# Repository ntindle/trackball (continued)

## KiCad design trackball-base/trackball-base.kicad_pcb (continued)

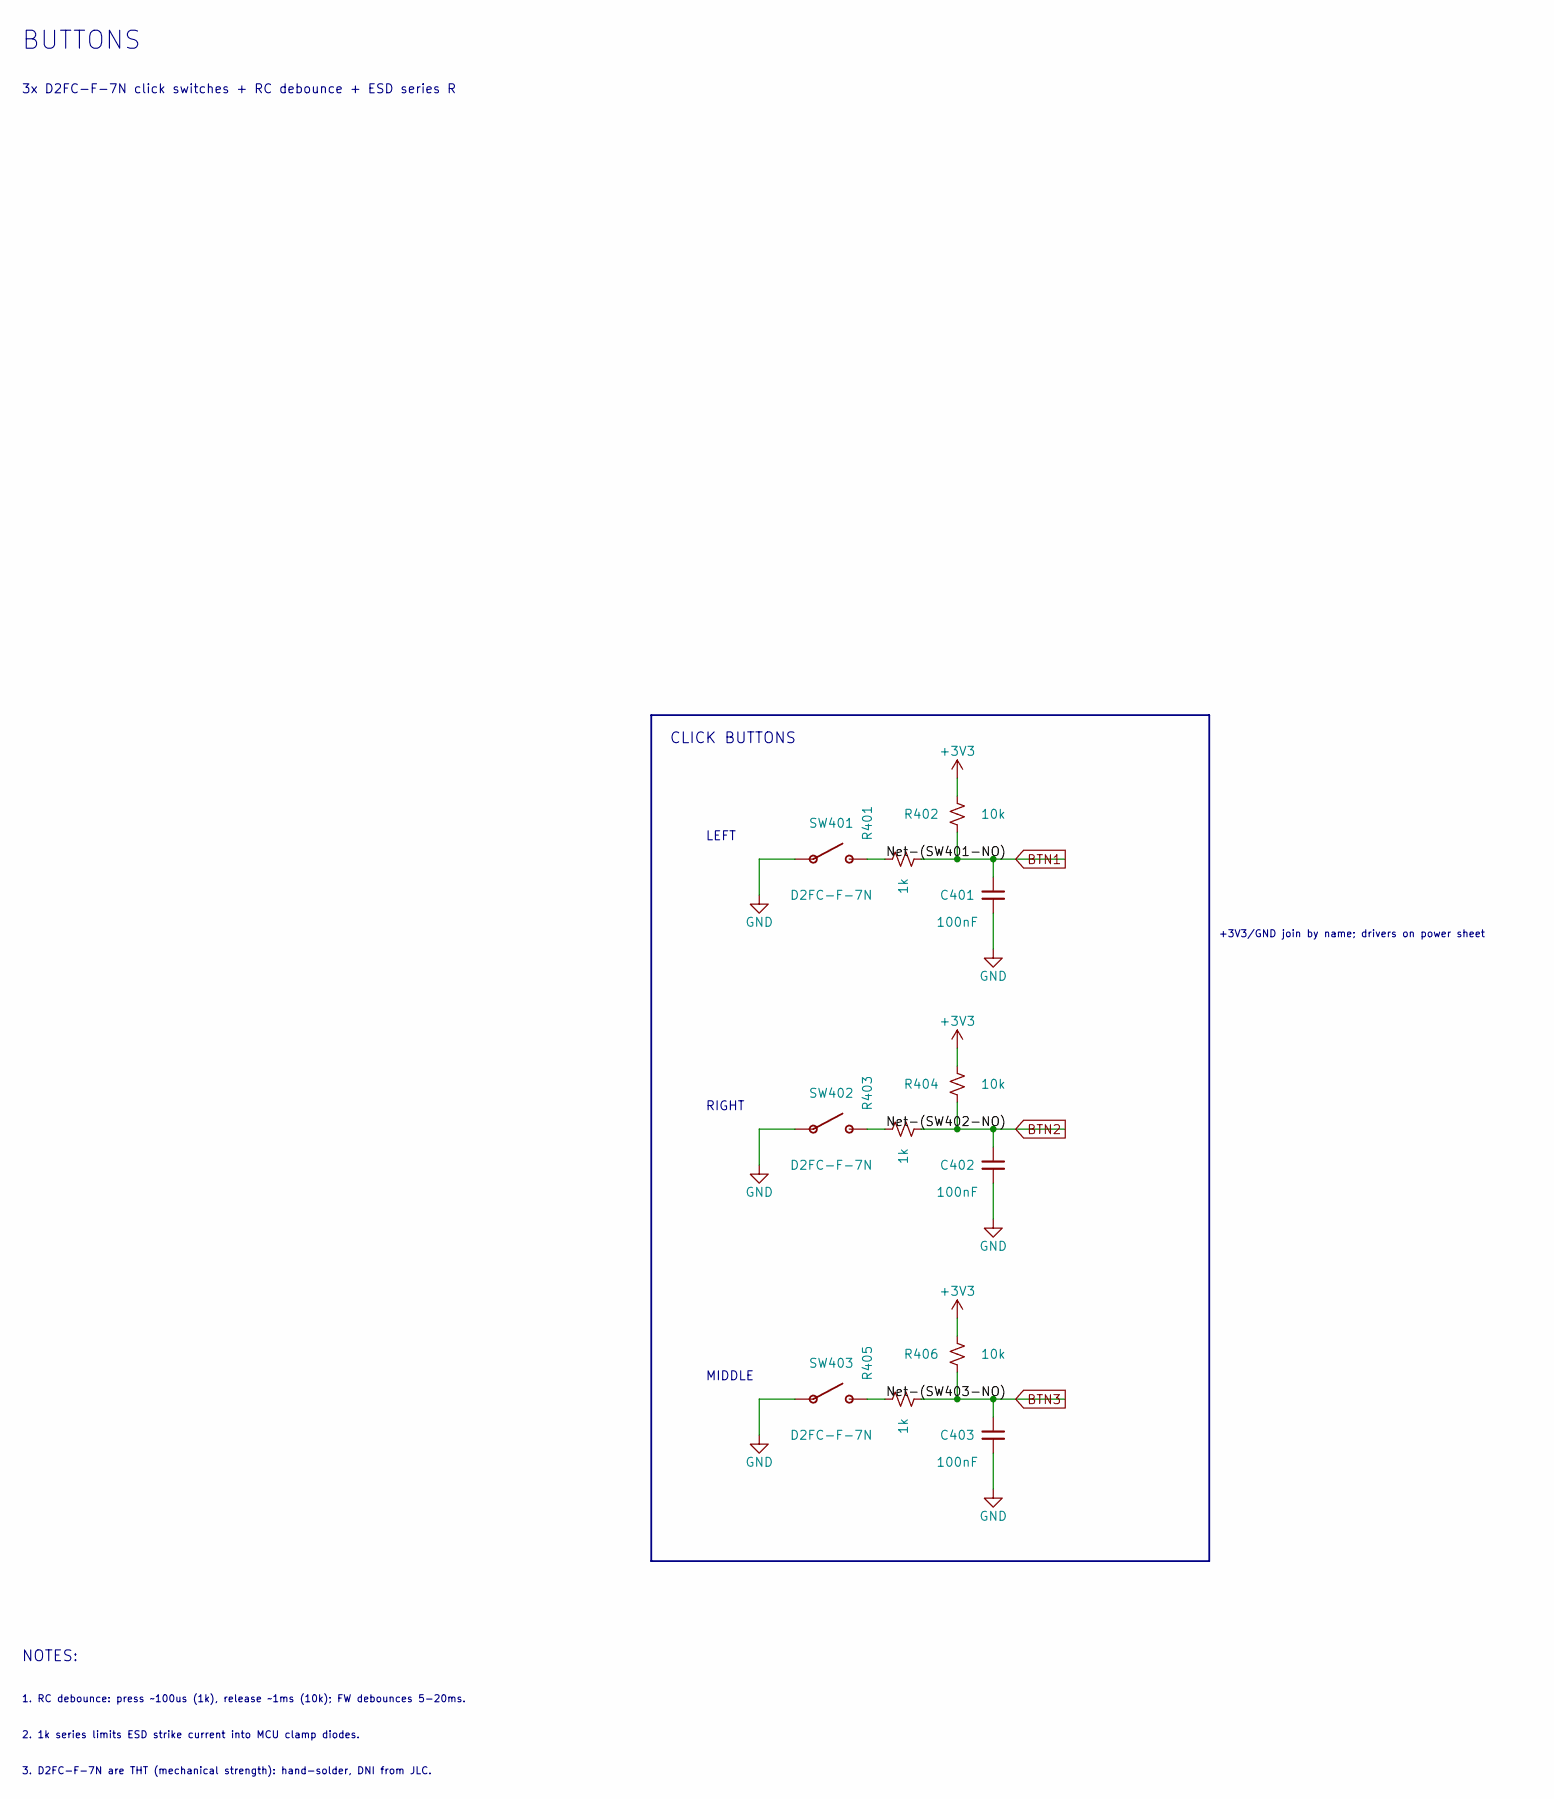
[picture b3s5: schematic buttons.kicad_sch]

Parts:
C401, C402, C403: 100nF; C_0603_1608Metric
R401, R403, R405: 1k; R_0603_1608Metric
R402, R404, R406: 10k; R_0603_1608Metric
SW401, SW402, SW403: D2FC-F-7N

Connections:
+3V3: R402.1, R404.1, R406.1; also elsewhere on the board
/buttons/Net-(SW401-NO): R401.1, SW401.2 (NO)
/buttons/Net-(SW402-NO): R403.1, SW402.2 (NO)
/buttons/Net-(SW403-NO): R405.1, SW403.2 (NO)
BTN1: C401.1, R401.2, R402.2; also elsewhere on the board
BTN2: C402.1, R403.2, R404.2; also elsewhere on the board
BTN3: C403.1, R405.2, R406.2; also elsewhere on the board

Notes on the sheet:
BUTTONS
3x D2FC-F-7N click switches + RC debounce + ESD series R
CLICK BUTTONS
LEFT
RIGHT
MIDDLE
+3V3/GND join by name; drivers on power sheet
NOTES:
1. RC debounce: press ~100us (1k), release ~1ms (10k); FW debounces 5-20ms.
2. 1k series limits ESD strike current into MCU clamp diodes.
3. D2FC-F-7N are THT (mechanical strength): hand-solder, DNI from JLC.

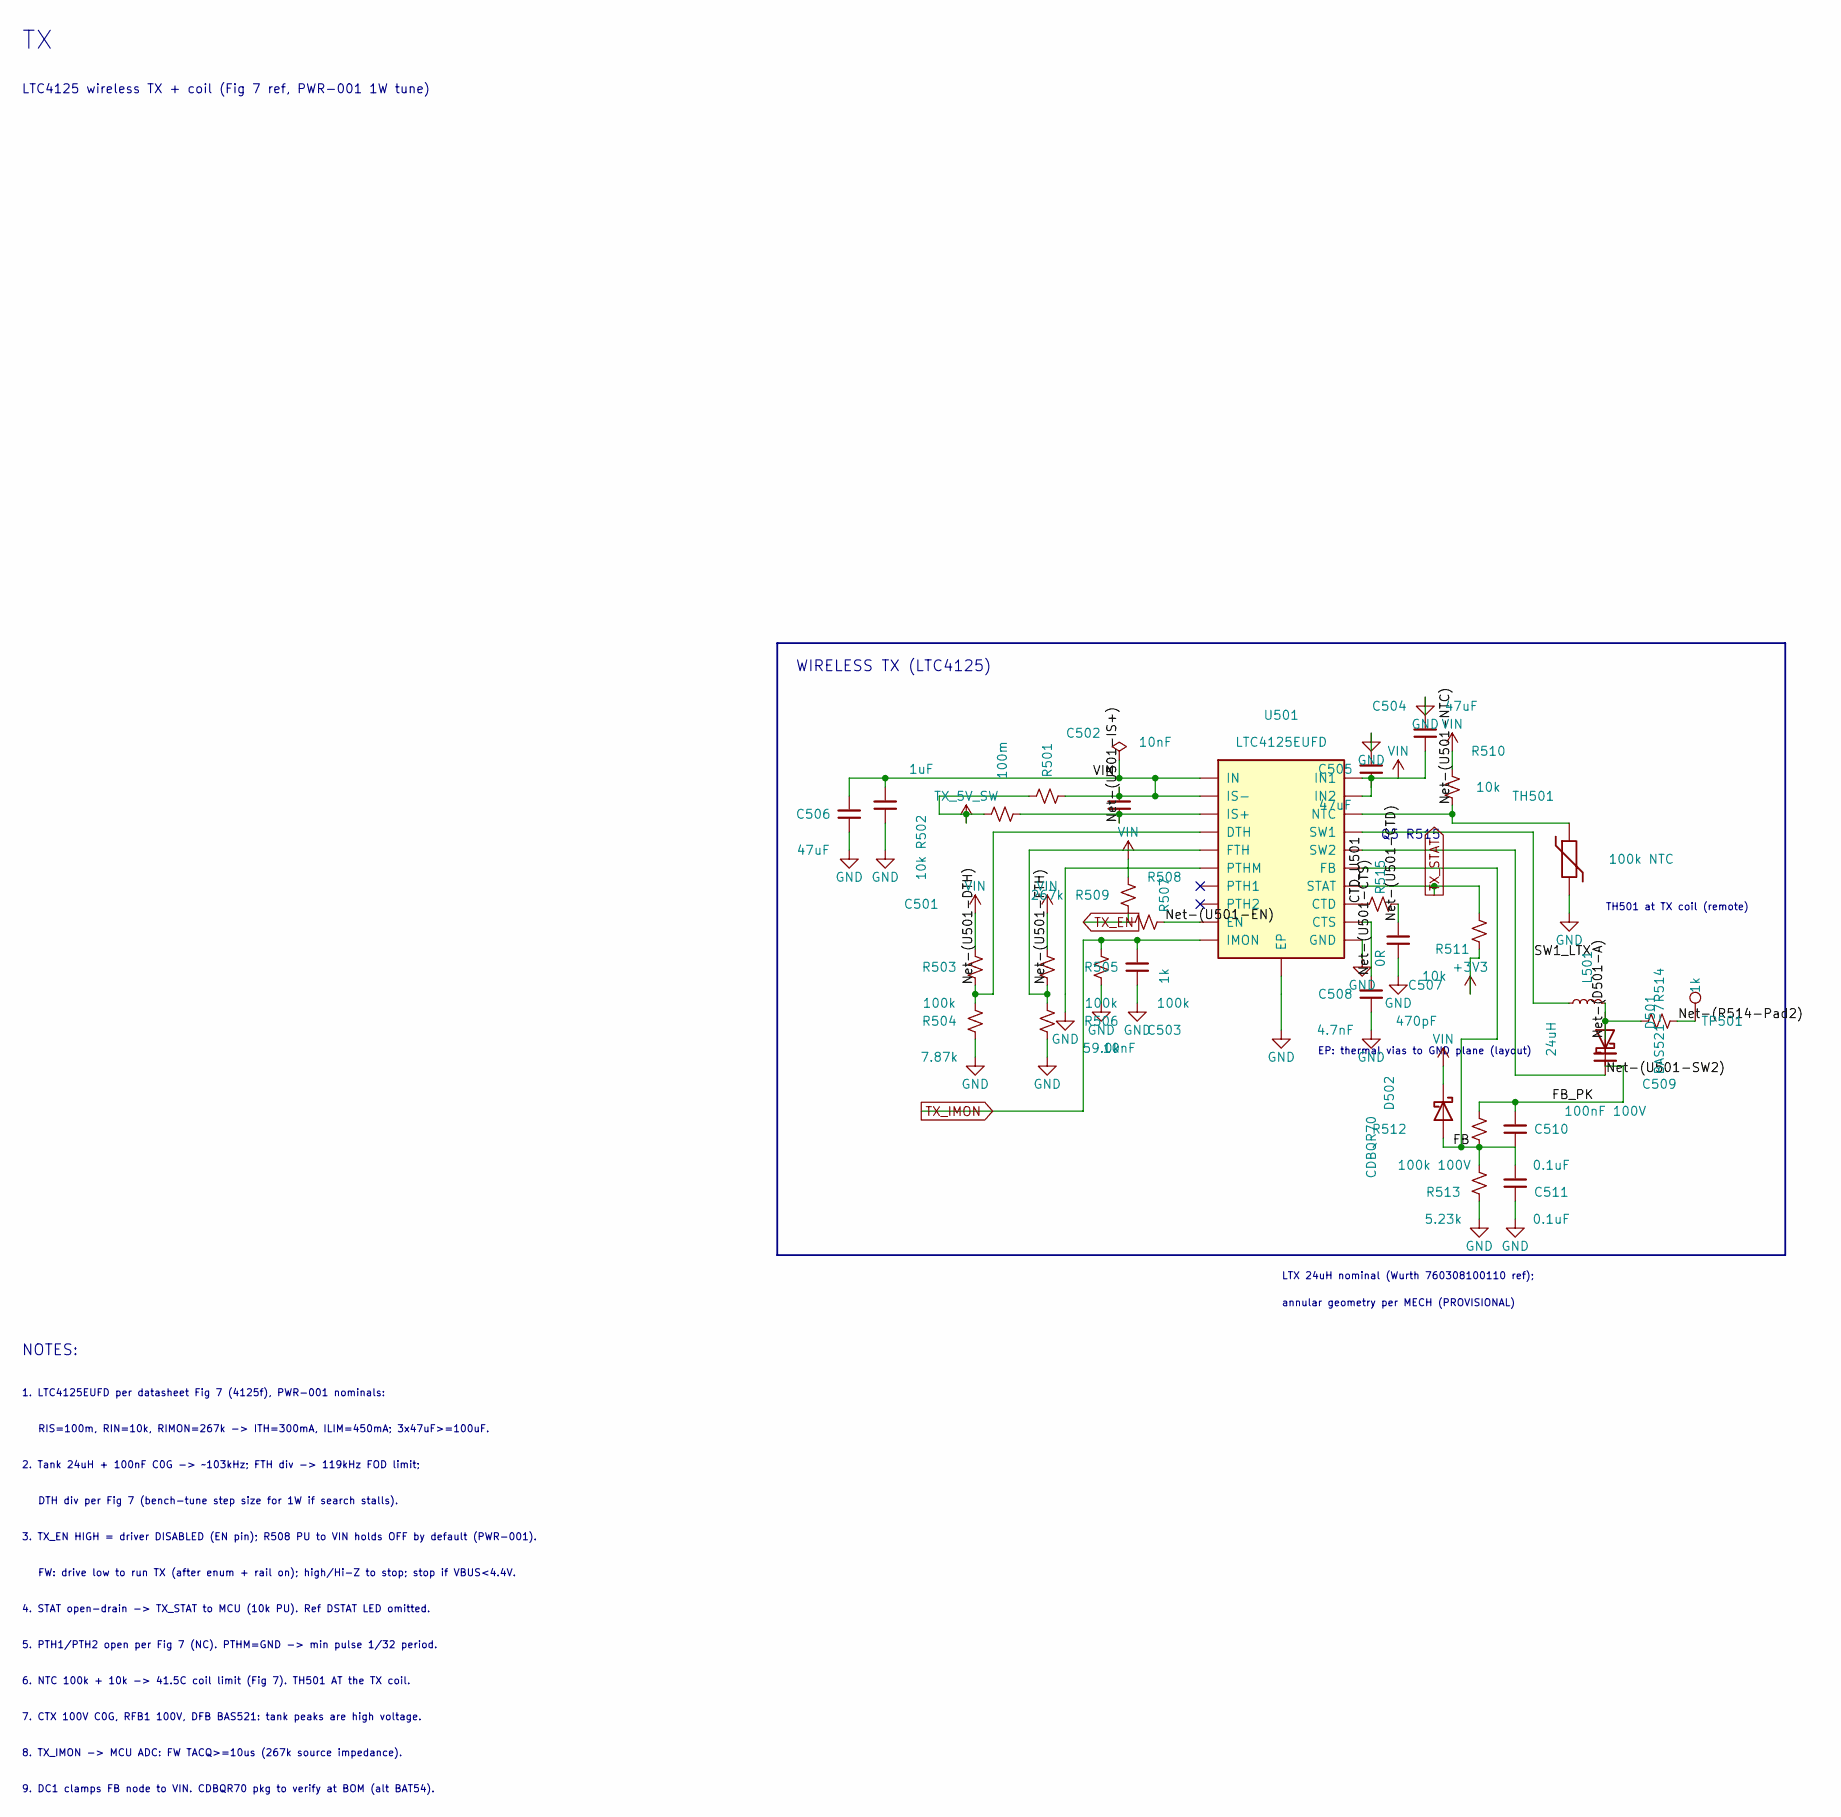
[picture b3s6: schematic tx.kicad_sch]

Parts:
C501: 1uF; C_0402_1005Metric
C502, C503: 10nF; C_0402_1005Metric
C504, C505, C506: 47uF; C_1206_3216Metric
C507: 470pF; C_0402_1005Metric
C508: 4.7nF; C_0402_1005Metric
C509: 100nF 100V; C_1206_3216Metric
C510, C511: 0.1uF; C_0402_1005Metric
D501: BAS521-7; D_SOD-523
D502: CDBQR70; D_0402_1005Metric
L501: 24uH; TX_COIL_IF_2P508
R501: 100m; R_1206_3216Metric
R502, R510, R511: 10k; R_0402_1005Metric
R503, R505, R508: 100k; R_0402_1005Metric
R504: 7.87k; R_0402_1005Metric
R506: 59.0k; R_0402_1005Metric
R507, R514: 1k; R_0402_1005Metric
R509: 267k; R_0402_1005Metric
R512: 100k 100V; R_1206_3216Metric
R513: 5.23k; R_0402_1005Metric
R515: 0R; R_0603_1608Metric
TH501: 100k NTC; R_0603_1608Metric
TP501: TP501; TestPoint_Pad_D1.5mm
U501: LTC4125EUFD; QFN-20-1EP_4x4mm_P0.5mm_EP2.5x2.5mm_ThermalVias

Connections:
+3V3: R511.2; also elsewhere on the board
/tx/CTD_U501: R515.1, U501.14 (CTD)
/tx/FB: C510.2, C511.1, D502.2 (A), R512.2, R513.1, U501.13 (FB)
/tx/FB_PK: C510.1, D501.1 (K), R512.1
/tx/Net-(D501-A): C509.1, D501.2 (A), L501.2, R514.1
/tx/Net-(R514-Pad2): R514.2, TP501.1
/tx/Net-(U501-CTD): C507.1, R515.2
/tx/Net-(U501-CTS): C508.1, U501.2 (CTS)
/tx/Net-(U501-DTH): R503.2, R504.1, U501.7 (DTH)
/tx/Net-(U501-EN): R507.2, U501.15 (EN)
/tx/Net-(U501-FTH): R505.2, R506.1, U501.9 (FTH)
/tx/Net-(U501-IS+): C502.2, R502.2, U501.4 (IS+)
/tx/Net-(U501-NTC): R510.2, TH501.1, U501.6 (NTC)
/tx/Net-(U501-SW2): C509.2, U501.18 (SW2)
/tx/SW1_LTX: L501.1, U501.19 (SW1)
TX_5V_SW: R501.1, R502.1; also elsewhere on the board
TX_EN: R507.1, R508.2; also elsewhere on the board
TX_IMON: C503.1, R509.1, U501.5 (IMON); also elsewhere on the board
TX_STAT: R511.1, U501.8 (STAT); also elsewhere on the board
VIN: C501.1, C502.1, C504.2, C505.2, C506.1, D502.1 (K), R501.2, R503.1, R505.1, R508.1, R510.1, U501.1 (IN), U501.3 (IS-), U501.17 (IN2), U501.20 (IN1)

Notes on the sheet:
LTC4125 wireless TX + coil (Fig 7 ref, PWR-001 1W tune)
WIRELESS TX (LTC4125)
EP: thermal vias to GND plane (layout)
TH501 at TX coil (remote)
LTX 24uH nominal (Wurth 760308100110 ref);
annular geometry per MECH (PROVISIONAL)
NOTES:
1. LTC4125EUFD per datasheet Fig 7 (4125f), PWR-001 nominals:
RIS=100m, RIN=10k, RIMON=267k -> ITH=300mA, ILIM=450mA; 3x47uF>=100uF.
2. Tank 24uH + 100nF C0G -> ~103kHz; FTH div -> 119kHz FOD limit;
DTH div per Fig 7 (bench-tune step size for 1W if search stalls).
3. TX_EN HIGH = driver DISABLED (EN pin); R508 PU to VIN holds OFF by default (PWR-001).
FW: drive low to run TX (after enum + rail on); high/Hi-Z to stop; stop if VBUS<4.4V.
4. STAT open-drain -> TX_STAT to MCU (10k PU). Ref DSTAT LED omitted.
5. PTH1/PTH2 open per Fig 7 (NC). PTHM=GND -> min pulse 1/32 period.
6. NTC 100k + 10k -> 41.5C coil limit (Fig 7). TH501 AT the TX coil.
7. CTX 100V C0G, RFB1 100V, DFB BAS521: tank peaks are high voltage.
8. TX_IMON -> MCU ADC: FW TACQ>=10us (267k source impedance).
9. DC1 clamps FB node to VIN. CDBQR70 pkg to verify at BOM (alt BAT54).
Q5 R515

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
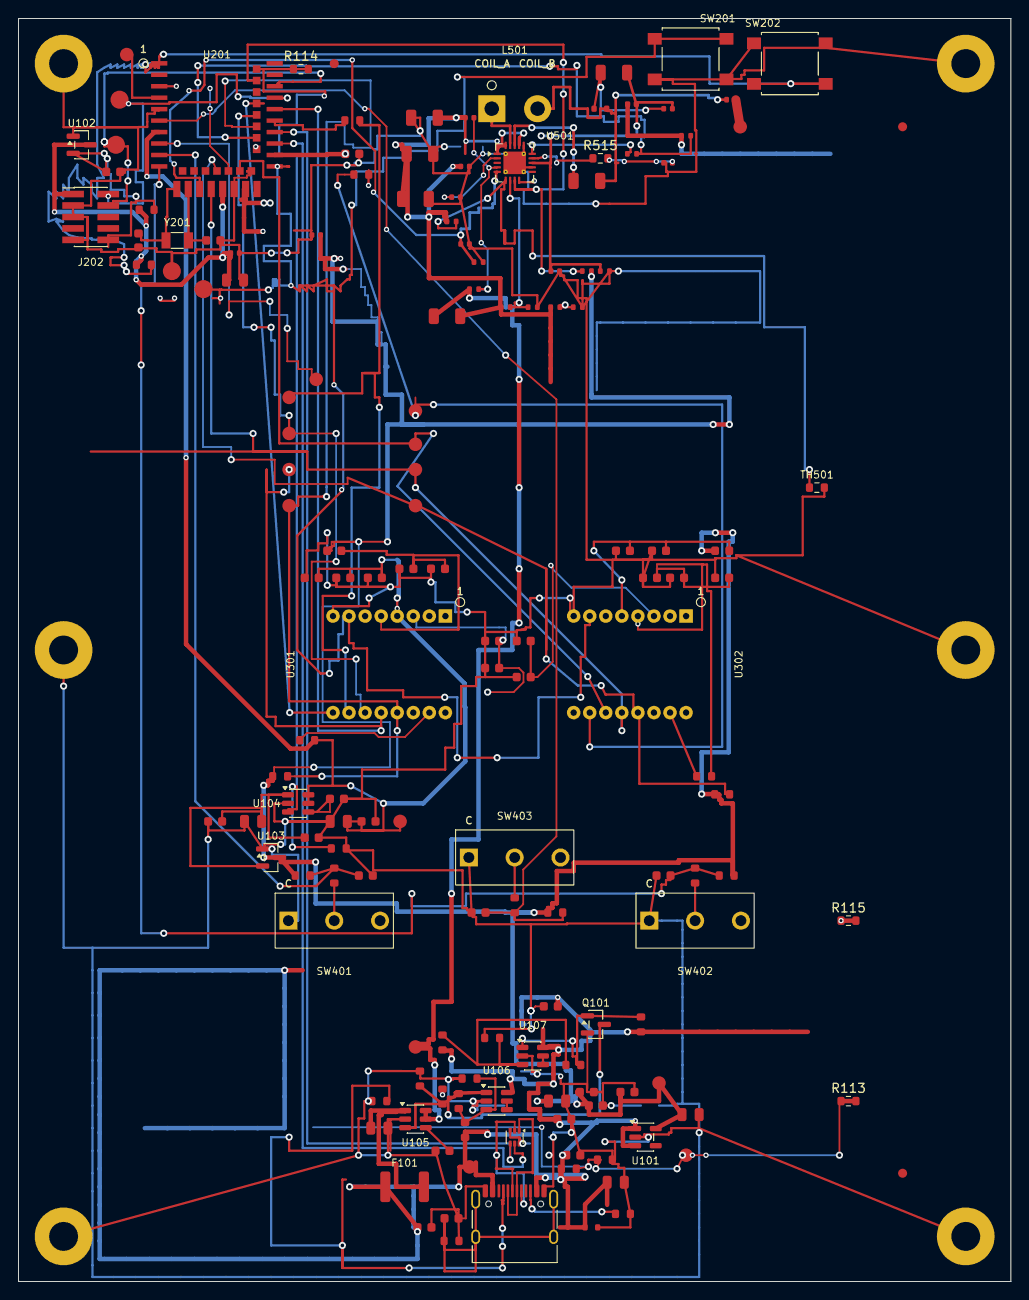
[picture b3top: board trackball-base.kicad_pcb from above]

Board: 4 copper layers, 110.0 x 140.0 mm, 159 parts (0 on the bottom side), 74 nets.

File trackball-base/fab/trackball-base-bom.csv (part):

"Reference","Value","Footprint","Datasheet"
"C101","10uF/16V","Capacitor_SMD:C_0805_2012Metric",""
"C102","100nF","Capacitor_SMD:C_0603_1608Metric",""
"C103","10uF/16V","Capacitor_SMD:C_0805_2012Metric",""
"C104","100nF","Capacitor_SMD:C_0603_1608Metric",""
"C105","100nF","Capacitor_SMD:C_0603_1608Metric",""
"C106","10uF/16V","Capacitor_SMD:C_0805_2012Metric",""
"C107","100nF","Capacitor_SMD:C_0603_1608Metric",""
"C108","10uF/16V","Capacitor_SMD:C_0805_2012Metric",""
"C109","100nF","Capacitor_SMD:C_0603_1608Metric",""
"C110","100nF","Capacitor_SMD:C_0603_1608Metric",""
"C111","4.7nF","Capacitor_SMD:C_0603_1608Metric",""
"C112","10uF/16V","Capacitor_SMD:C_0805_2012Metric",""
"C113","100nF","Capacitor_SMD:C_0603_1608Metric",""
"C114","10uF/16V","Capacitor_SMD:C_0805_2012Metric",""
"C115","100nF","Capacitor_SMD:C_0603_1608Metric",""
"C116","4.7nF","Capacitor_SMD:C_0603_1608Metric",""
"C117","100nF","Capacitor_SMD:C_0603_1608Metric",""
"C118","100nF","Capacitor_SMD:C_0603_1608Metric",""
"C201","12pF","Capacitor_SMD:C_0603_1608Metric",""
"C202","12pF","Capacitor_SMD:C_0603_1608Metric",""
"C203","100nF","Capacitor_SMD:C_0402_1005Metric",""
"C204","100nF","Capacitor_SMD:C_0402_1005Metric",""
"C205","1uF/16V","Capacitor_SMD:C_0603_1608Metric",""
"C206","100nF","Capacitor_SMD:C_0603_1608Metric",""
"C207","10uF/10V","Capacitor_SMD:C_0805_2012Metric",""
"C208","4.7nF","Capacitor_SMD:C_0603_1608Metric",""
"C301","1uF","Capacitor_SMD:C_0603_1608Metric",""
"C302","100nF","Capacitor_SMD:C_0603_1608Metric",""
"C303","4.7uF","Capacitor_SMD:C_0603_1608Metric",""
"C304","1uF","Capacitor_SMD:C_0603_1608Metric",""
"C305","100nF","Capacitor_SMD:C_0603_1608Metric",""
"C306","1uF","Capacitor_SMD:C_0603_1608Metric",""
"C307","100nF","Capacitor_SMD:C_0603_1608Metric",""
"C308","1uF","Capacitor_SMD:C_0603_1608Metric",""
"C309","100nF","Capacitor_SMD:C_0603_1608Metric",""
"C310","4.7uF","Capacitor_SMD:C_0603_1608Metric",""
"C311","1uF","Capacitor_SMD:C_0603_1608Metric",""
"C312","100nF","Capacitor_SMD:C_0603_1608Metric",""
"C313","1uF","Capacitor_SMD:C_0603_1608Metric",""
"C314","100nF","Capacitor_SMD:C_0603_1608Metric",""
"C401","100nF","Capacitor_SMD:C_0603_1608Metric",""
"C402","100nF","Capacitor_SMD:C_0603_1608Metric",""
"C403","100nF","Capacitor_SMD:C_0603_1608Metric",""
"C501","1uF","Capacitor_SMD:C_0402_1005Metric",""
"C502","10nF","Capacitor_SMD:C_0402_1005Metric",""
"C503","10nF","Capacitor_SMD:C_0402_1005Metric",""
"C504","47uF","Capacitor_SMD:C_1206_3216Metric",""
"C505","47uF","Capacitor_SMD:C_1206_3216Metric",""
"C506","47uF","Capacitor_SMD:C_1206_3216Metric",""
"C507","470pF","Capacitor_SMD:C_0402_1005Metric",""
"C508","4.7nF","Capacitor_SMD:C_0402_1005Metric",""
"C509","100nF 100V","Capacitor_SMD:C_1206_3216Metric",""
"C510","0.1uF","Capacitor_SMD:C_0402_1005Metric",""
"C511","0.1uF","Capacitor_SMD:C_0402_1005Metric",""
"D203","ESD5Z5.0T1G","Diode_SMD:D_SOD-523","https://www.onsemi.com/pdf/datasheet/esd5z2v5t1-d.pdf"
"D501","BAS521-7","Diode_SMD:D_SOD-523",""
"D502","CDBQR70","Diode_SMD:D_0402_1005Metric",""
"F101","MF-MSMF050-2","Fuse:Fuse_1812_4532Metric",""
"FB301","600R","Inductor_SMD:L_0603_1608Metric",""
"FB302","600R","Inductor_SMD:L_0603_1608Metric",""
"J201","TYPE-C-31-M-12","Connector_USB:USB_C_Receptacle_HRO_TYPE-C-31-M-12",""
"J202","CORTEX-DBG-10","Connector_PinHeader_1.27mm:PinHeader_2x05_P1.27mm_Vertical_SMD",""
"L501","24uH","trackball:TX_COIL_IF_2P508",""
"Q101","2N7002","Package_TO_SOT_SMD:SOT-23",""
"R101","100k","Resistor_SMD:R_0603_1608Metric",""
"R102","100k","Resistor_SMD:R_0603_1608Metric",""
"R103","100k","Resistor_SMD:R_0603_1608Metric",""
"R104","100k","Resistor_SMD:R_0603_1608Metric",""
"R105","37.4k","Resistor_SMD:R_0603_1608Metric",""
"R106","1M","Resistor_SMD:R_0603_1608Metric",""
"R107","100k","Resistor_SMD:R_0603_1608Metric",""
"R108","27.4k","Resistor_SMD:R_0603_1608Metric",""
"R109","6.8M","Resistor_SMD:R_0603_1608Metric",""
"R110","100k","Resistor_SMD:R_0603_1608Metric",""
"R111","10k","Resistor_SMD:R_0603_1608Metric",""
"R112","100k","Resistor_SMD:R_0603_1608Metric",""
"R113","0R","Resistor_SMD:R_0603_1608Metric",""
"R114","0R","Resistor_SMD:R_0603_1608Metric",""
"R115","0R","Resistor_SMD:R_0603_1608Metric",""
"R201","10k","Resistor_SMD:R_0603_1608Metric",""
"R202","10k","Resistor_SMD:R_0603_1608Metric",""
"R203","5.1k","Resistor_SMD:R_0603_1608Metric",""
"R204","5.1k","Resistor_SMD:R_0603_1608Metric",""
"R205","1M","Resistor_SMD:R_0603_1608Metric",""
"R206","33","Resistor_SMD:R_0603_1608Metric",""
"R207","33","Resistor_SMD:R_0603_1608Metric",""
"R301","10k","Resistor_SMD:R_0603_1608Metric",""
"R302","39","Resistor_SMD:R_0603_1608Metric",""
"R303","10k","Resistor_SMD:R_0603_1608Metric",""
"R304","39","Resistor_SMD:R_0603_1608Metric",""
"R401","1k","Resistor_SMD:R_0603_1608Metric",""
"R402","10k","Resistor_SMD:R_0603_1608Metric",""
"R403","1k","Resistor_SMD:R_0603_1608Metric",""
"R404","10k","Resistor_SMD:R_0603_1608Metric",""
"R405","1k","Resistor_SMD:R_0603_1608Metric",""
"R406","10k","Resistor_SMD:R_0603_1608Metric",""
"R501","100m","Resistor_SMD:R_1206_3216Metric",""
"R502","10k","Resistor_SMD:R_0402_1005Metric",""
"R503","100k","Resistor_SMD:R_0402_1005Metric",""
"R504","7.87k","Resistor_SMD:R_0402_1005Metric",""
"R505","100k","Resistor_SMD:R_0402_1005Metric",""
"R506","59.0k","Resistor_SMD:R_0402_1005Metric",""
"R507","1k","Resistor_SMD:R_0402_1005Metric",""
"R508","100k","Resistor_SMD:R_0402_1005Metric",""
"R509","267k","Resistor_SMD:R_0402_1005Metric",""
"R510","10k","Resistor_SMD:R_0402_1005Metric",""
"R511","10k","Resistor_SMD:R_0402_1005Metric",""
"R512","100k 100V","Resistor_SMD:R_1206_3216Metric",""
"R513","5.23k","Resistor_SMD:R_0402_1005Metric",""
"R514","1k","Resistor_SMD:R_0402_1005Metric",""
"R515","0R","Resistor_SMD:R_0603_1608Metric",""
"SW201","RESET","Button_Switch_SMD:SW_SPST_B3S-1000",""
"SW202","BOOT","Button_Switch_SMD:SW_SPST_B3S-1000",""
"SW401","D2FC-F-7N","trackball:D2FC-F-7N","Omron D2F/D2FC series"
"SW402","D2FC-F-7N","trackball:D2FC-F-7N","Omron D2F/D2FC series"
"SW403","D2FC-F-7N","trackball:D2FC-F-7N","Omron D2F/D2FC series"
"TH501","100k NTC","Resistor_SMD:R_0603_1608Metric",""
"TP101","TP101","TestPoint:TestPoint_Pad_D1.5mm",""
"TP102","TP102","TestPoint:TestPoint_Pad_D1.5mm",""
"TP103","TP103","TestPoint:TestPoint_Pad_D1.5mm",""
"TP104","TP104","TestPoint:TestPoint_Pad_D1.5mm",""
"TP105","TP105","TestPoint:TestPoint_Pad_D1.5mm",""
"TP201","UART_TXD","TestPoint:TestPoint_Pad_D1.5mm",""
"TP202","UART_RXD","TestPoint:TestPoint_Pad_D1.5mm",""
"TP203","TP203","TestPoint:TestPoint_Pad_D2.0mm",""
"TP204","TP204","TestPoint:TestPoint_Pad_D2.0mm",""
"TP205","TP205","TestPoint:TestPoint_Pad_D2.0mm",""
"TP206","TP206","TestPoint:TestPoint_Pad_D2.0mm",""
"TP301","TP301","TestPoint:TestPoint_Pad_D1.5mm",""
"TP302","TP302","TestPoint:TestPoint_Pad_D1.5mm",""
"TP303","TP303","TestPoint:TestPoint_Pad_D1.5mm",""
"TP304","TP304","TestPoint:TestPoint_Pad_D1.5mm",""
"TP305","TP305","TestPoint:TestPoint_Pad_D1.5mm",""
"TP306","TP306","TestPoint:TestPoint_Pad_D1.5mm",""
"TP307","TP307","TestPoint:TestPoint_Pad_D1.5mm",""
"TP308","TP308","TestPoint:TestPoint_Pad_D1.5mm",""
"TP501","TP501","TestPoint:TestPoint_Pad_D1.5mm",""
"U101","AP2112K-3.3TRG1","Package_TO_SOT_SMD:SOT-23-5",""
"U102","APX809-29SAG-7","Package_TO_SOT_SMD:SOT-23",""
"U103","XC6206P192MR","Package_TO_SOT_SMD:SOT-23",""
"U104","TPS22918DBVR","Package_TO_SOT_SMD:SOT-23-6",""
"U105","TPS22918DBVR","Package_TO_SOT_SMD:SOT-23-6",""
"U106","TLV3011AIDBVR","Package_TO_SOT_SMD:SOT-23-6",""
"U107","TLV3011AIDBVR","Package_TO_SOT_SMD:SOT-23-6",""
"U201","E73-2G4M08S1C","trackball:E73-2G4M08S1C","https://www.cdebyte.com/products/E73-2G4M08S1C"
"U202","TPD2E1B06DRLR","Package_TO_SOT_SMD:SOT-563",""
"U301","PMW3360DM-T2QU","trackball:PMW3360DM-T2QU","PMW3360 datasheet v1.50"
"U302","PMW3360DM-T2QU","trackball:PMW3360DM-T2QU","PMW3360 datasheet v1.50"
"U501","LTC4125EUFD","Package_DFN_QFN:QFN-20-1EP_4x4mm_P0.5mm_EP2.5x2.5mm_ThermalVias",""
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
